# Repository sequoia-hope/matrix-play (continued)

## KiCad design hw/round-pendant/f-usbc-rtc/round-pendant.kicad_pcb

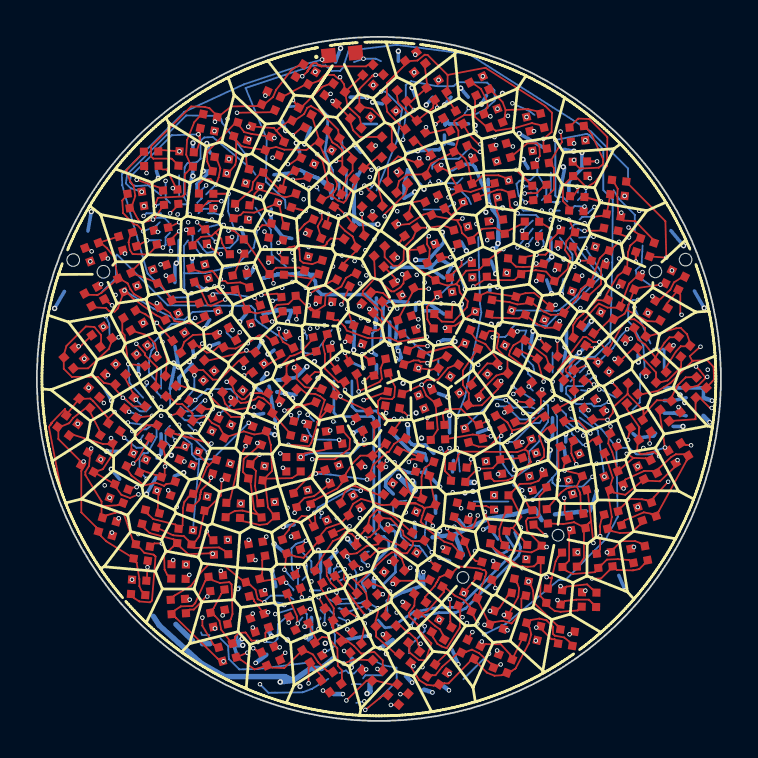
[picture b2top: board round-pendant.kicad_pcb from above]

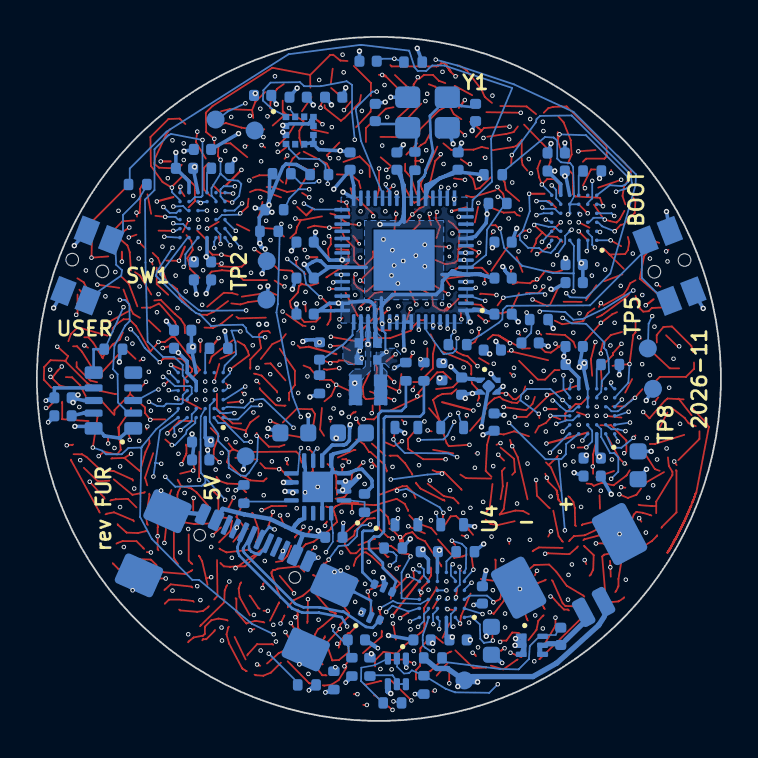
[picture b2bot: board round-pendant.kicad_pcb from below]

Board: 8 copper layers, 38.0 x 38.0 mm, 346 parts (110 on the bottom side), 187 nets.

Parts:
BT1: A1251WR-S-2P; Molex_PicoBlade_53261-0271_1x02-1MP_P1.25mm_Horizontal
C1, C3, C4, C31, C34, C41, C44, C51, C54, C61, C64, C71, C74, C76: 1u; C_0402_1005Metric
C2, C30, C40: 22u; C_0603_1608Metric
C5: 10u; C_0603_1608Metric
C6, C7, C8, C9, C10, C11, C12, C13, C14, C20, C21, C22, C25, C27, C32, C33, C35, C42, C43, C52, C53, C62, C63, C70, C72, C73, C75: 100n; C_0402_1005Metric
C16, C18: 4.7u; C_0402_1005Metric_small_pads
C17, C19, C26: 4.7u; C_0402_1005Metric
C23, C24: 15p; C_0402_1005Metric
D1, D2, D3, D4, D5, D6, D7, D8, D9, D10, D11, D12, D13, D14, D15, D16, D17, D18, D19, D20, D21, D22, D23, D24, D25, D26, D27, D28, D29, D30, D31, D32, D33, D34, D35, D36, D37, D38, D39, D40, D41, D42, D43, D44, D45, D46, D47, D48, D49, D50, D51, D52, D53, D54, D55, D56, D57, D58, D59, D60, D61, D62, D63, D64, D65, D66, D67, D68, D69, D70, D71, D72, D73, D74, D75, D76, D77, D78, D79, D80, D81, D82, D83, D84, D85, D86, D87, D88, D89, D90, D91, D92, D93, D94, D95, D96, D97, D98, D99, D100, D101, D102, D103, D104, D105, D106, D107, D108, D109, D110, D111, D112, D113, D114, D115, D116, D117, D118, D119, D120, D121, D122, D123, D124, D125, D126, D127, D128, D129, D130, D131, D132, D133, D134, D135, D136, D137, D138, D139, D140, D141, D142, D143, D144, D145, D146, D147, D148, D149, D150, D151, D152, D153, D154, D155, D156, D157, D158, D159, D160, D161, D162, D163, D164, D165, D166, D167, D168, D169, D170, D171, D172, D173, D174, D175, D176, D177, D178, D179, D180, D181, D182, D183, D184, D185, D186, D187, D188, D189, D190, D191, D192, D193, D194, D195, D196, D197, D198, D199, D200, D201, D202, D203, D204, D205, D206, D207, D208, D209, D210, D211, D212, D213, D214, D215, D216, D217, D218, D219, D220, D221, D222, D223, D224, D225, D226, D227, D228, D229, D230, D231, D232, D233, D234, D235: RGB; LED_XL-1010RGB
J1: TYPE-C-31-M-22; USB_C_Receptacle_Hroparts_TYPE-C-31-M-22
L1: 3.3u; L_pol_2016
Q1: NTZD3155C; SOT-563
Q2: ALS-PT19; SENSOR_ALS-PT19
R1, R2: 5.1k; R_0402_1005Metric
R3: 10k; R_0402_1005Metric
R4: 3k; R_0402_1005Metric
R5: 3.6k; R_0402_1005Metric
R6, R7, R9, R10, R11, R12, R31, R32: 100k; R_0402_1005Metric
R8: 100R; R_0402_1005Metric
R13: 33R; R_0402_1005Metric
R14, R15: 27R; R_0402_1005Metric
R16, R17, R18, R21, R22: 1k; R_0402_1005Metric
R19, R20: 4.7k; R_0402_1005Metric
R30, R33, R50, R60, R70: 30k; R_0402_1005Metric
R43: 22k; R_0402_1005Metric
SW1: USER / WAKE; SW_Panasonic_EVQP7C
SW2: BOOTSEL; SW_Panasonic_EVQP7C
TP1: VSYS; TestPoint_Pad_D1.0mm
TP2: +3V3; TestPoint_Pad_D1.0mm
TP3: VBAT; TestPoint_Pad_D1.0mm
TP4: 1V1; TestPoint_Pad_D1.0mm
TP5: RUN; TestPoint_Pad_D1.0mm
TP6: SWCLK; TestPoint_Pad_D1.0mm
TP7: SWDIO; TestPoint_Pad_D1.0mm
TP8: GND; TestPoint_Pad_D1.0mm
U1, U2, U10, U11, U12: IS31FL3745; WLCSP-36_2.9x2.9mm_P0.5mm
U3: RP2350A; RP2350-QFN-60-1EP_7x7_P0.4mm_EP3.4x3.4mm_ThermalVias
U4: W25Q128JVPIQ; WSON-8_6x5mm_P1.27mm_NoEPCopper
U5: BQ24073; QFN-16-1EP_3x3mm_P0.5mm_EP1.7x1.7mm
U6: TPS7A0233; Texas_X2SON-4_1x1mm_P0.65mm
U7: USBLC6-2P6; SOT-666
U8: XB9901A; XySemi_DFN-6_1.8x1.4mm
U9: LIS2DW12; LGA-12_2x2mm_P0.5mm
U13: RX8130CE; Seiko_Epson_RX8130CE_3.2x2.5mm_P0.7mm
Y1: 12MHz; Crystal_SMD_3225-4Pin_3.2x2.5mm

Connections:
+1V1: C18.1, C19.1, C20.1, C21.1, L1.1, TP4.1, U3.6, U3.23, U3.39, U3.50
+3V3: C4.1, C8.1, C9.1, C10.1, C11.1, C12.1, C13.1, C14.1, C16.1, C22.1, C25.1, C26.1, C27.1, C75.1, R6.1, R7.1, R13.1, R19.1, R20.1, R21.1, R22.1, R32.1, TP2.1, U3.1, U3.11, U3.20, U3.30, U3.38, U3.44, U3.45, U3.49, U3.53, U3.54, U4.8, U5.6, U6.1, U9.2, U9.3, U9.9, U9.10, U13.1, U13.8, U13.10
/Driver 1 and matrix/CS1_1: D1.4, D2.4, D3.4, D4.4, D5.4, D6.4, D7.4, D8.4, U1.B2
/Driver 1 and matrix/CS1_2: D1.2, D2.2, D3.2, D4.2, D5.2, D6.2, D7.2, D8.2, U1.B3
/Driver 1 and matrix/CS1_3: D1.1, D2.1, D3.1, D4.1, D5.1, D6.1, D7.1, D8.1, U1.C3
/Driver 1 and matrix/CS1_4: D9.4, D10.4, D11.4, D12.4, D13.4, D14.4, D15.4, D16.4, U1.C2
/Driver 1 and matrix/CS1_5: D9.2, D10.2, D11.2, D12.2, D13.2, D14.2, D15.2, D16.2, U1.D2
/Driver 1 and matrix/CS1_6: D9.1, D10.1, D11.1, D12.1, D13.1, D14.1, D15.1, D16.1, U1.D1
/Driver 1 and matrix/CS1_7: D17.4, D18.4, D19.4, D20.4, D21.4, D22.4, D23.4, D24.4, U1.E2
/Driver 1 and matrix/CS1_8: D17.2, D18.2, D19.2, D20.2, D21.2, D22.2, D23.2, D24.2, U1.E1
/Driver 1 and matrix/CS1_9: D17.1, D18.1, D19.1, D20.1, D21.1, D22.1, D23.1, D24.1, U1.F1
/Driver 1 and matrix/CS1_10: D25.4, D26.4, D27.4, D28.4, D29.4, D30.4, D31.4, D32.4, U1.F6
/Driver 1 and matrix/CS1_11: D25.2, D26.2, D27.2, D28.2, D29.2, D30.2, D31.2, D32.2, U1.E6
/Driver 1 and matrix/CS1_12: D25.1, D26.1, D27.1, D28.1, D29.1, D30.1, D31.1, D32.1, U1.D5
/Driver 1 and matrix/CS1_13: D33.4, D34.4, D35.4, D36.4, D37.4, D38.4, D39.4, D40.4, U1.D6
/Driver 1 and matrix/CS1_14: D33.2, D34.2, D35.2, D36.2, D37.2, D38.2, D39.2, D40.2, U1.C4
/Driver 1 and matrix/CS1_15: D33.1, D34.1, D35.1, D36.1, D37.1, D38.1, D39.1, D40.1, U1.C6
/Driver 1 and matrix/CS1_16: D41.4, D42.4, D43.4, D44.4, D45.4, D46.4, D47.4, U1.C5
/Driver 1 and matrix/CS1_17: D41.2, D42.2, D43.2, D44.2, D45.2, D46.2, D47.2, U1.B4
/Driver 1 and matrix/CS1_18: D41.1, D42.1, D43.1, D44.1, D45.1, D46.1, D47.1, U1.B5
/Driver 1 and matrix/SW1_1: D1.3, D9.3, D17.3, D25.3, D33.3, D41.3, U1.A2
/Driver 1 and matrix/SW1_2: D2.3, D10.3, D18.3, D26.3, D34.3, D42.3, U1.A4
/Driver 1 and matrix/SW1_3: D3.3, D11.3, D19.3, D27.3, D35.3, D43.3, U1.A1
/Driver 1 and matrix/SW1_4: D4.3, D12.3, D20.3, D28.3, D36.3, D44.3, U1.A5
/Driver 1 and matrix/SW1_5: D5.3, D13.3, D21.3, D29.3, D37.3, D45.3, U1.B1
/Driver 1 and matrix/SW1_6: D6.3, D14.3, D22.3, D30.3, D38.3, D46.3, U1.A6
/Driver 1 and matrix/SW1_7: D7.3, D15.3, D23.3, D31.3, D39.3, D47.3, U1.C1
/Driver 1 and matrix/SW1_8: D8.3, D16.3, D24.3, D32.3, D40.3, U1.B6
/Driver 2 and matrix/CS2_1: D48.4, D49.4, D50.4, D51.4, D52.4, D53.4, D54.4, D55.4, U2.B2
/Driver 2 and matrix/CS2_2: D48.2, D49.2, D50.2, D51.2, D52.2, D53.2, D54.2, D55.2, U2.B3
/Driver 2 and matrix/CS2_3: D48.1, D49.1, D50.1, D51.1, D52.1, D53.1, D54.1, D55.1, U2.C3
/Driver 2 and matrix/CS2_4: D56.4, D57.4, D58.4, D59.4, D60.4, D61.4, D62.4, D63.4, U2.C2
/Driver 2 and matrix/CS2_5: D56.2, D57.2, D58.2, D59.2, D60.2, D61.2, D62.2, D63.2, U2.D2
/Driver 2 and matrix/CS2_6: D56.1, D57.1, D58.1, D59.1, D60.1, D61.1, D62.1, D63.1, U2.D1
/Driver 2 and matrix/CS2_7: D64.4, D65.4, D66.4, D67.4, D68.4, D69.4, D70.4, D71.4, U2.E2
/Driver 2 and matrix/CS2_8: D64.2, D65.2, D66.2, D67.2, D68.2, D69.2, D70.2, D71.2, U2.E1
/Driver 2 and matrix/CS2_9: D64.1, D65.1, D66.1, D67.1, D68.1, D69.1, D70.1, D71.1, U2.F1
/Driver 2 and matrix/CS2_10: D72.4, D73.4, D74.4, D75.4, D76.4, D77.4, D78.4, D79.4, U2.F6
/Driver 2 and matrix/CS2_11: D72.2, D73.2, D74.2, D75.2, D76.2, D77.2, D78.2, D79.2, U2.E6
/Driver 2 and matrix/CS2_12: D72.1, D73.1, D74.1, D75.1, D76.1, D77.1, D78.1, D79.1, U2.D5
/Driver 2 and matrix/CS2_13: D80.4, D81.4, D82.4, D83.4, D84.4, D85.4, D86.4, D87.4, U2.D6
/Driver 2 and matrix/CS2_14: D80.2, D81.2, D82.2, D83.2, D84.2, D85.2, D86.2, D87.2, U2.C4
/Driver 2 and matrix/CS2_15: D80.1, D81.1, D82.1, D83.1, D84.1, D85.1, D86.1, D87.1, U2.C6
/Driver 2 and matrix/CS2_16: D88.4, D89.4, D90.4, D91.4, D92.4, D93.4, D94.4, U2.C5
/Driver 2 and matrix/CS2_17: D88.2, D89.2, D90.2, D91.2, D92.2, D93.2, D94.2, U2.B4
/Driver 2 and matrix/CS2_18: D88.1, D89.1, D90.1, D91.1, D92.1, D93.1, D94.1, U2.B5
/Driver 2 and matrix/SW2_1: D48.3, D56.3, D64.3, D72.3, D80.3, D88.3, U2.A2
/Driver 2 and matrix/SW2_2: D49.3, D57.3, D65.3, D73.3, D81.3, D89.3, U2.A4
/Driver 2 and matrix/SW2_3: D50.3, D58.3, D66.3, D74.3, D82.3, D90.3, U2.A1
/Driver 2 and matrix/SW2_4: D51.3, D59.3, D67.3, D75.3, D83.3, D91.3, U2.A5
/Driver 2 and matrix/SW2_5: D52.3, D60.3, D68.3, D76.3, D84.3, D92.3, U2.B1
/Driver 2 and matrix/SW2_6: D53.3, D61.3, D69.3, D77.3, D85.3, D93.3, U2.A6
/Driver 2 and matrix/SW2_7: D54.3, D62.3, D70.3, D78.3, D86.3, D94.3, U2.C1
/Driver 2 and matrix/SW2_8: D55.3, D63.3, D71.3, D79.3, D87.3, U2.B6
/Driver 3 and matrix/CS3_1: D95.4, D96.4, D97.4, D98.4, D99.4, D100.4, D101.4, D102.4, U10.B2
/Driver 3 and matrix/CS3_2: D95.2, D96.2, D97.2, D98.2, D99.2, D100.2, D101.2, D102.2, U10.B3
/Driver 3 and matrix/CS3_3: D95.1, D96.1, D97.1, D98.1, D99.1, D100.1, D101.1, D102.1, U10.C3
/Driver 3 and matrix/CS3_4: D103.4, D104.4, D105.4, D106.4, D107.4, D108.4, D109.4, D110.4, U10.C2
/Driver 3 and matrix/CS3_5: D103.2, D104.2, D105.2, D106.2, D107.2, D108.2, D109.2, D110.2, U10.D2
/Driver 3 and matrix/CS3_6: D103.1, D104.1, D105.1, D106.1, D107.1, D108.1, D109.1, D110.1, U10.D1
/Driver 3 and matrix/CS3_7: D111.4, D112.4, D113.4, D114.4, D115.4, D116.4, D117.4, D118.4, U10.E2
/Driver 3 and matrix/CS3_8: D111.2, D112.2, D113.2, D114.2, D115.2, D116.2, D117.2, D118.2, U10.E1
/Driver 3 and matrix/CS3_9: D111.1, D112.1, D113.1, D114.1, D115.1, D116.1, D117.1, D118.1, U10.F1
/Driver 3 and matrix/CS3_10: D119.4, D120.4, D121.4, D122.4, D123.4, D124.4, D125.4, D126.4, U10.F6
/Driver 3 and matrix/CS3_11: D119.2, D120.2, D121.2, D122.2, D123.2, D124.2, D125.2, D126.2, U10.E6
/Driver 3 and matrix/CS3_12: D119.1, D120.1, D121.1, D122.1, D123.1, D124.1, D125.1, D126.1, U10.D5
/Driver 3 and matrix/CS3_13: D127.4, D128.4, D129.4, D130.4, D131.4, D132.4, D133.4, D134.4, U10.D6
/Driver 3 and matrix/CS3_14: D127.2, D128.2, D129.2, D130.2, D131.2, D132.2, D133.2, D134.2, U10.C4
/Driver 3 and matrix/CS3_15: D127.1, D128.1, D129.1, D130.1, D131.1, D132.1, D133.1, D134.1, U10.C6
/Driver 3 and matrix/CS3_16: D135.4, D136.4, D137.4, D138.4, D139.4, D140.4, D141.4, U10.C5
/Driver 3 and matrix/CS3_17: D135.2, D136.2, D137.2, D138.2, D139.2, D140.2, D141.2, U10.B4
/Driver 3 and matrix/CS3_18: D135.1, D136.1, D137.1, D138.1, D139.1, D140.1, D141.1, U10.B5
/Driver 3 and matrix/SW3_1: D95.3, D103.3, D111.3, D119.3, D127.3, D135.3, U10.A2
/Driver 3 and matrix/SW3_2: D96.3, D104.3, D112.3, D120.3, D128.3, D136.3, U10.A4
/Driver 3 and matrix/SW3_3: D97.3, D105.3, D113.3, D121.3, D129.3, D137.3, U10.A1
/Driver 3 and matrix/SW3_4: D98.3, D106.3, D114.3, D122.3, D130.3, D138.3, U10.A5
/Driver 3 and matrix/SW3_5: D99.3, D107.3, D115.3, D123.3, D131.3, D139.3, U10.B1
/Driver 3 and matrix/SW3_6: D100.3, D108.3, D116.3, D124.3, D132.3, D140.3, U10.A6
/Driver 3 and matrix/SW3_7: D101.3, D109.3, D117.3, D125.3, D133.3, D141.3, U10.C1
/Driver 3 and matrix/SW3_8: D102.3, D110.3, D118.3, D126.3, D134.3, U10.B6
/Driver 4 and matrix/CS4_1: D142.4, D143.4, D144.4, D145.4, D146.4, D147.4, D148.4, D149.4, U11.B2
/Driver 4 and matrix/CS4_2: D142.2, D143.2, D144.2, D145.2, D146.2, D147.2, D148.2, D149.2, U11.B3
/Driver 4 and matrix/CS4_3: D142.1, D143.1, D144.1, D145.1, D146.1, D147.1, D148.1, D149.1, U11.C3
/Driver 4 and matrix/CS4_4: D150.4, D151.4, D152.4, D153.4, D154.4, D155.4, D156.4, D157.4, U11.C2
/Driver 4 and matrix/CS4_5: D150.2, D151.2, D152.2, D153.2, D154.2, D155.2, D156.2, D157.2, U11.D2
/Driver 4 and matrix/CS4_6: D150.1, D151.1, D152.1, D153.1, D154.1, D155.1, D156.1, D157.1, U11.D1
/Driver 4 and matrix/CS4_7: D158.4, D159.4, D160.4, D161.4, D162.4, D163.4, D164.4, D165.4, U11.E2
/Driver 4 and matrix/CS4_8: D158.2, D159.2, D160.2, D161.2, D162.2, D163.2, D164.2, D165.2, U11.E1
/Driver 4 and matrix/CS4_9: D158.1, D159.1, D160.1, D161.1, D162.1, D163.1, D164.1, D165.1, U11.F1
/Driver 4 and matrix/CS4_10: D166.4, D167.4, D168.4, D169.4, D170.4, D171.4, D172.4, D173.4, U11.F6
/Driver 4 and matrix/CS4_11: D166.2, D167.2, D168.2, D169.2, D170.2, D171.2, D172.2, D173.2, U11.E6
/Driver 4 and matrix/CS4_12: D166.1, D167.1, D168.1, D169.1, D170.1, D171.1, D172.1, D173.1, U11.D5
/Driver 4 and matrix/CS4_13: D174.4, D175.4, D176.4, D177.4, D178.4, D179.4, D180.4, D181.4, U11.D6
/Driver 4 and matrix/CS4_14: D174.2, D175.2, D176.2, D177.2, D178.2, D179.2, D180.2, D181.2, U11.C4
/Driver 4 and matrix/CS4_15: D174.1, D175.1, D176.1, D177.1, D178.1, D179.1, D180.1, D181.1, U11.C6
/Driver 4 and matrix/CS4_16: D182.4, D183.4, D184.4, D185.4, D186.4, D187.4, D188.4, U11.C5
/Driver 4 and matrix/CS4_17: D182.2, D183.2, D184.2, D185.2, D186.2, D187.2, D188.2, U11.B4
/Driver 4 and matrix/CS4_18: D182.1, D183.1, D184.1, D185.1, D186.1, D187.1, D188.1, U11.B5
/Driver 4 and matrix/SW4_1: D142.3, D150.3, D158.3, D166.3, D174.3, D182.3, U11.A2
/Driver 4 and matrix/SW4_2: D143.3, D151.3, D159.3, D167.3, D175.3, D183.3, U11.A4
/Driver 4 and matrix/SW4_3: D144.3, D152.3, D160.3, D168.3, D176.3, D184.3, U11.A1
/Driver 4 and matrix/SW4_4: D145.3, D153.3, D161.3, D169.3, D177.3, D185.3, U11.A5
/Driver 4 and matrix/SW4_5: D146.3, D154.3, D162.3, D170.3, D178.3, D186.3, U11.B1
/Driver 4 and matrix/SW4_6: D147.3, D155.3, D163.3, D171.3, D179.3, D187.3, U11.A6
/Driver 4 and matrix/SW4_7: D148.3, D156.3, D164.3, D172.3, D180.3, D188.3, U11.C1
/Driver 4 and matrix/SW4_8: D149.3, D157.3, D165.3, D173.3, D181.3, U11.B6
/Driver 5 and matrix/CS5_1: D189.4, D190.4, D191.4, D192.4, D193.4, D194.4, D195.4, D196.4, U12.B2
/Driver 5 and matrix/CS5_2: D189.2, D190.2, D191.2, D192.2, D193.2, D194.2, D195.2, D196.2, U12.B3
/Driver 5 and matrix/CS5_3: D189.1, D190.1, D191.1, D192.1, D193.1, D194.1, D195.1, D196.1, U12.C3
/Driver 5 and matrix/CS5_4: D197.4, D198.4, D199.4, D200.4, D201.4, D202.4, D203.4, D204.4, U12.C2
/Driver 5 and matrix/CS5_5: D197.2, D198.2, D199.2, D200.2, D201.2, D202.2, D203.2, D204.2, U12.D2
/Driver 5 and matrix/CS5_6: D197.1, D198.1, D199.1, D200.1, D201.1, D202.1, D203.1, D204.1, U12.D1
/Driver 5 and matrix/CS5_7: D205.4, D206.4, D207.4, D208.4, D209.4, D210.4, D211.4, D212.4, U12.E2
/Driver 5 and matrix/CS5_8: D205.2, D206.2, D207.2, D208.2, D209.2, D210.2, D211.2, D212.2, U12.E1
/Driver 5 and matrix/CS5_9: D205.1, D206.1, D207.1, D208.1, D209.1, D210.1, D211.1, D212.1, U12.F1
/Driver 5 and matrix/CS5_10: D213.4, D214.4, D215.4, D216.4, D217.4, D218.4, D219.4, D220.4, U12.F6
/Driver 5 and matrix/CS5_11: D213.2, D214.2, D215.2, D216.2, D217.2, D218.2, D219.2, D220.2, U12.E6
/Driver 5 and matrix/CS5_12: D213.1, D214.1, D215.1, D216.1, D217.1, D218.1, D219.1, D220.1, U12.D5
/Driver 5 and matrix/CS5_13: D221.4, D222.4, D223.4, D224.4, D225.4, D226.4, D227.4, D228.4, U12.D6
/Driver 5 and matrix/CS5_14: D221.2, D222.2, D223.2, D224.2, D225.2, D226.2, D227.2, D228.2, U12.C4
/Driver 5 and matrix/CS5_15: D221.1, D222.1, D223.1, D224.1, D225.1, D226.1, D227.1, D228.1, U12.C6
/Driver 5 and matrix/CS5_16: D229.4, D230.4, D231.4, D232.4, D233.4, D234.4, D235.4, U12.C5
/Driver 5 and matrix/CS5_17: D229.2, D230.2, D231.2, D232.2, D233.2, D234.2, D235.2, U12.B4
/Driver 5 and matrix/CS5_18: D229.1, D230.1, D231.1, D232.1, D233.1, D234.1, D235.1, U12.B5
/Driver 5 and matrix/SW5_1: D189.3, D197.3, D205.3, D213.3, D221.3, D229.3, U12.A2
/Driver 5 and matrix/SW5_2: D190.3, D198.3, D206.3, D214.3, D222.3, D230.3, U12.A4
/Driver 5 and matrix/SW5_3: D191.3, D199.3, D207.3, D215.3, D223.3, D231.3, U12.A1
/Driver 5 and matrix/SW5_4: D192.3, D200.3, D208.3, D216.3, D224.3, D232.3, U12.A5
/Driver 5 and matrix/SW5_5: D193.3, D201.3, D209.3, D217.3, D225.3, D233.3, U12.B1
/Driver 5 and matrix/SW5_6: D194.3, D202.3, D210.3, D218.3, D226.3, D234.3, U12.A6
/Driver 5 and matrix/SW5_7: D195.3, D203.3, D211.3, D219.3, D227.3, D235.3, U12.C1
/Driver 5 and matrix/SW5_8: D196.3, D204.3, D212.3, D220.3, D228.3, U12.B6
/MCU/ACC_INT: U3.14, U9.12
/MCU/ACC_SCL: R19.2, U3.5, U9.1, U13.2
/MCU/ACC_SDA: R20.2, U3.4, U9.4, U13.3
/MCU/BTN: R18.1, U3.15
/MCU/LIGHT: C70.1, Q2.2, R43.1, U3.41
/MCU/LIGHT_PWR: Q2.1, U3.3
/MCU/QSPI_SCLK: U3.56, U4.6
/MCU/QSPI_SD0: U3.57, U4.5
/MCU/QSPI_SD1: U3.59, U4.2
/MCU/QSPI_SD2: U3.58, U4.3
/MCU/QSPI_SD3: U3.55, U4.7
/MCU/QSPI_SS: R16.1, U3.60, U4.1
/MCU/RTC_INT: R32.2, U3.31, U13.6
/MCU/RTC_VOUT: C76.1, U13.9
/MCU/RUN: TP5.1, U3.26
/MCU/SWCLK: TP6.1, U3.24
/MCU/SWDIO: TP7.1, U3.25
/MCU/USB_DM_MCU: R14.2, U3.51
/MCU/USB_DP_MCU: R15.2, U3.52
/MCU/VREG_AVDD: C17.1, R13.2, U3.46
/MCU/VREG_LX: L1.2, U3.48
/Power/BAT_N: BT1.2, C6.2, U8.4, U8.5
/Power/CC1: J1.A5, R1.1
/Power/CC2: J1.B5, R2.1
/Power/USB_DM_C: J1.A7, J1.B7, U7.1
/Power/USB_DP_C: J1.A6, J1.B6, U7.3
CHG: R7.2, U3.16, U5.9
GND: BT1.MP, C1.2, C2.2, C3.2, C4.2, C5.2, C7.2, C8.2, C9.2, C10.2, C11.2, C12.2, C13.2, C14.2, C16.2, C17.2, C18.2, C19.2, C20.2, C21.2, C22.2, C23.2, C24.2, C25.2, C26.2, C27.2, C30.2, C31.2, C32.2, C33.2, C34.2, C35.2, C40.2, C41.2, C42.2, C43.2, C44.2, C51.2, C52.2, C53.2, C54.2, C61.2, C62.2, C63.2, C64.2, C70.2, C71.2, C72.2, C73.2, C74.2, C75.2, C76.2, J1.A1B12, J1.B1A12, J1.S1, Q1.1, R1.2, R2.2, R3.2, R4.2, R5.2, R9.2, R12.2, R30.2, R31.2, R33.2, R43.2, R50.2, R60.2, R70.2, SW1.2, SW2.2, TP8.1, U1.D4, U1.E4, U1.F4, U2.E4, U2.F4, U3.47, U3.61, U4.4, U5.4, U5.5, U5.8, U5.15, U5.17, U6.2, U6.5, U7.2, U8.1, U8.2, U8.3, U9.6, U9.7, U9.8, U10.F4, U11.F4, U12.F4, U13.7, Y1.2, Y1.4
I2C_SCL: R22.2, U1.E3, U2.E3, U3.8, U10.D4, U10.E3, U10.E4, U11.E3, U11.E4, U12.E3
I2C_SDA: R21.2, U1.D3, U2.D3, U2.D4, U3.7, U10.D3, U11.D3, U11.D4, U12.D3
LED_SDB: C35.1, R31.1, U1.E5, U2.E5, U3.9, U10.E5, U11.E5, U12.E5
unnamed: C24.1, R17.1, Y1.3
unnamed: Q1.5, Q1.6, R10.2
unnamed: Q1.3, R11.1
unnamed: R16.2, SW2.1
unnamed: R18.2, SW1.1
unnamed: R30.1, U1.F3
unnamed: R33.1, U2.F3
unnamed: C23.1, U3.21, Y1.1
unnamed: R17.2, U3.22
unnamed: R5.1, U5.12
unnamed: R4.1, U5.16
unnamed: R3.1, U5.1
unnamed: C6.1, R8.2, U8.6
unnamed: R50.1, U10.F3
unnamed: R60.1, U11.F3
unnamed: R70.1, U12.F3
PGOOD: R6.2, U3.17, U5.7
USB_DM: R14.1, U7.6
USB_DP: R15.1, U7.4
VBAT: BT1.1, C5.1, Q1.4, R8.1, R10.1, TP3.1, U5.2, U5.3
VBAT_EN: Q1.2, R9.1, U3.18
VBAT_SENSE: C7.1, R11.2, R12.1, U3.40
VBUS: C1.1, J1.A4B9, J1.B4A9, U5.13, U7.5
VSYS: C2.1, C3.1, C30.1, C31.1, C32.1, C33.1, C34.1, C40.1, C41.1, C42.1, C43.1, C44.1, C51.1, C52.1, C53.1, C54.1, C61.1, C62.1, C63.1, C64.1, C71.1, C72.1, C73.1, C74.1, TP1.1, U1.A3, U1.F5, U2.A3, U2.F5, U5.10, U5.11, U6.3, U6.4, U10.A3, U10.F5, U11.A3, U11.F5, U12.A3, U12.D4, U12.E4, U12.F5

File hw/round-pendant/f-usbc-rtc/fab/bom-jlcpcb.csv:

Comment,Designator,Footprint,LCSC Part #,MPN,Manufacturer
A1251WR-S-2P,BT1,Molex_PicoBlade_53261-0271_1x02-1MP_P1.25mm_Horizontal,C225111,A1251WR-S-2P,CJT
1u,"C1,C3,C4,C31,C34,C41,C44,C51,C54,C61,C64,C71,C74,C76",C_0402_1005Metric,C52923,CL05A105KA5NQNC,Samsung Electro-Mechanics
22u,"C2,C30,C40",C_0603_1608Metric,C86295,CL10A226MP8NUNE,Samsung Electro-Mechanics
10u,C5,C_0603_1608Metric,C19702,CL10A106KP8NNNC,Samsung Electro-Mechanics
100n,"C6,C7,C8,C9,C10,C11,C12,C13,C14,C20,C21,C22,C25,C27,C32,C33,C35,C42,C43,C52,C53,C62,C63,C70,C72,C73,C75",C_0402_1005Metric,C1525,CL05B104KO5NNNC,Samsung Electro-Mechanics
4.7u,"C16,C18",C_0402_1005Metric_small_pads,C23733,CL05A475MP5NRNC,Samsung Electro-Mechanics
4.7u,"C17,C19,C26",C_0402_1005Metric,C23733,CL05A475MP5NRNC,Samsung Electro-Mechanics
15p,"C23,C24",C_0402_1005Metric,C1548,0402CG150J500NT,FH
RGB,"D1,D2,D3,D4,D5,D6,D7,D8,D9,D10,D11,D12,D13,D14,D15,D16,D17,D18,D19,D20,D21,D22,D23,D24,D25,D26,D27,D28,D29,D30,D31,D32,D33,D34,D35,D36,D37,D38,D39,D40,D41,D42,D43,D44,D45,D46,D47,D48,D49,D50,D51,D52,D53,D54,D55,D56,D57,D58,D59,D60,D61,D62,D63,D64,D65,D66,D67,D68,D69,D70,D71,D72,D73,D74,D75,D76,D77,D78,D79,D80,D81,D82,D83,D84,D85,D86,D87,D88,D89,D90,D91,D92,D93,D94,D95,D96,D97,D98,D99,D100,D101,D102,D103,D104,D105,D106,D107,D108,D109,D110,D111,D112,D113,D114,D115,D116,D117,D118,D119,D120,D121,D122,D123,D124,D125,D126,D127,D128,D129,D130,D131,D132,D133,D134,D135,D136,D137,D138,D139,D140,D141,D142,D143,D144,D145,D146,D147,D148,D149,D150,D151,D152,D153,D154,D155,D156,D157,D158,D159,D160,D161,D162,D163,D164,D165,D166,D167,D168,D169,D170,D171,D172,D173,D174,D175,D176,D177,D178,D179,D180,D181,D182,D183,D184,D185,D186,D187,D188,D189,D190,D191,D192,D193,D194,D195,D196,D197,D198,D199,D200,D201,D202,D203,D204,D205,D206,D207,D208,D209,D210,D211,D212,D213,D214,D215,D216,D217,D218,D219,D220,D221,D222,D223,D224,D225,D226,D227,D228,D229,D230,D231,D232,D233,D234,D235",LED_XL-1010RGB,C965834,XL-1010RGB-YG,XINGLIGHT
TYPE-C-31-M-22,J1,USB_C_Receptacle_Hroparts_TYPE-C-31-M-22,C530612,TYPE-C-31-M-22,Korean Hroparts Elec
3.3u,L1,L_pol_2016,C42411119,AOTA-B201610S3R3-101-T,Abracon
NTZD3155C,Q1,SOT-563,C236117,NTZD3155CT1G,onsemi
ALS-PT19,Q2,SENSOR_ALS-PT19,C146233,ALS-PT19-315C/L177/TR8,EVERLIGHT
5.1k,"R1,R2",R_0402_1005Metric,C25905,0402WGF5101TCE,UNI-ROYAL
10k,R3,R_0402_1005Metric,C25744,0402WGF1002TCE,UNI-ROYAL
3k,R4,R_0402_1005Metric,C25784,0402WGF3001TCE,UNI-ROYAL
3.6k,R5,R_0402_1005Metric,C25891,0402WGF3601TCE,UNI-ROYAL
100k,"R6,R7,R9,R10,R11,R12,R31,R32",R_0402_1005Metric,C25741,0402WGF1003TCE,UNI-ROYAL
100R,R8,R_0402_1005Metric,C25076,0402WGF1000TCE,UNI-ROYAL
33R,R13,R_0402_1005Metric,C25105,0402WGF330JTCE,UNI-ROYAL
27R,"R14,R15",R_0402_1005Metric,C25100,0402WGF270JTCE,UNI-ROYAL
1k,"R16,R17,R18,R21,R22",R_0402_1005Metric,C11702,0402WGF1001TCE,UNI-ROYAL
4.7k,"R19,R20",R_0402_1005Metric,C25900,0402WGF4701TCE,UNI-ROYAL
30k,"R30,R33,R50,R60,R70",R_0402_1005Metric,C25776,0402WGF3002TCE,UNI-ROYAL
22k,R43,R_0402_1005Metric,C25768,0402WGF2202TCE,UNI-ROYAL
USER / WAKE,SW1,SW_Panasonic_EVQP7C,C388883,EVQP7C01P,PANASONIC
BOOTSEL,SW2,SW_Panasonic_EVQP7C,C388883,EVQP7C01P,PANASONIC
IS31FL3745,"U1,U2,U10,U11,U12",WLCSP-36_2.9x2.9mm_P0.5mm,C2678907,IS31FL3745-CLS4-TR,ISSI
RP2350A,U3,RP2350-QFN-60-1EP_7x7_P0.4mm_EP3.4x3.4mm_ThermalVias,C42411118,RP2350A,Raspberry Pi
W25Q128JVPIQ,U4,WSON-8_6x5mm_P1.27mm_NoEPCopper,C190862,W25Q128JVPIQ,Winbond
BQ24073,U5,QFN-16-1EP_3x3mm_P0.5mm_EP1.7x1.7mm,C15220,BQ24073RGTR,Texas Instruments
TPS7A0233,U6,Texas_X2SON-4_1x1mm_P0.65mm,C2860046,TPS7A0233PDQNR,Texas Instruments
USBLC6-2P6,U7,SOT-666,C15999,USBLC6-2P6,STMicroelectronics
XB9901A,U8,XySemi_DFN-6_1.8x1.4mm,C669687,XB9901A,XySemi
LIS2DW12,U9,LGA-12_2x2mm_P0.5mm,C189624,LIS2DW12TR,STMicroelectronics
RX8130CE,U13,Seiko_Epson_RX8130CE_3.2x2.5mm_P0.7mm,C1542426,RX8130CE:BB,Seiko Epson
12MHz,Y1,Crystal_SMD_3225-4Pin_3.2x2.5mm,C20625731,ABM8-272-T3,Abracon

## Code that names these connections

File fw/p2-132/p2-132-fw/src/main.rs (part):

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//! - Enables Cortex-M33 VFPv5 FPU, 12 MHz XOSC, and 150 MHz PLL_SYS + 1 us TIMER0 tick.
//! - Configures PADS_QSPI SLEWFAST=0 (Phase P1 EM finding: cuts In2.Cu QSPI crosstalk 5.1x).
//! - Drives U1 (0x20, North 6x11 D1..D66) and U2 (0x25, South 6x11 D67..D132) over 1.04 MHz Fm+
//!   open-drain I2C on GPIO4/GPIO5 using RP2350 PIO0 SM0 + DMA Channel 0 (DREQ_PIO0_TX0 = 0).
//! - Programs AW20198QNR EM-derived registers:
//!     * SRCR (0x2B) = 0x07 (6 ns rise / 10 ns fall -> 3.4x lower I2C glitch & -30.4 dB @ 300 MHz EMI)
//!     * PCCR (0x29) = 0x02 (Three-Phase PWM stagger -> 5.4x lower VSYS AC ripple at North U1)
//!     * SSCR (0x28) = 0x15 (Spread-spectrum clock modulation enabled)
//!     * DGCR (0x02) = 0x44 (Off-time 4 kOhm CS pull-up / 2 kOhm SW bleed de-ghosting)
//!     * SL0..197    = D65 white-balanced per-die current scaling (R=255, G=96, B=220)
//! - Polls LIS2DW12TR (0x19) on GPIO2/GPIO3 (400 kHz open-drain SIO I2C), SW1 button (GPIO11),
//!   BQ24073 status (GPIO12 CHG, GPIO13 PGOOD), and 8x-oversampled ADC0/ADC1 (VBAT_SENSE / LIGHT,
//!   averaging out the 148 mV VREG_LX buck crossover spikes discovered in Phase P2!).
//! - Applies our Phase P4 PDN-derived GCC(VBAT) foldback curve below 3.65 V to prevent North Blue/Green dropout.
//! - Dual-core pipelined architecture:
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const RESET_TIMER0: u32     = 1 << 23;

// p2-132 GPIO Pinout
const PIN_LIGHT_PWR: u32 = 1;
const PIN_ACC_SDA: u32   = 2;
const PIN_ACC_SCL: u32   = 3;
const PIN_I2C_SDA: u32   = 4;
const PIN_I2C_SCL: u32   = 5;
const PIN_LED_SDB: u32   = 6;
const PIN_ACC_INT: u32   = 10;
const PIN_BTN: u32       = 11;
const PIN_CHG: u32       = 12;
const PIN_PGOOD: u32     = 13;
const PIN_VBAT_EN: u32   = 14;
const PIN_VBAT_ADC: u32  = 26;
const PIN_LIGHT_ADC: u32 = 27;

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
    // Configure digital pads (clear RP2350 ISO bit 8, enable IE bit 6, 4 mA drive, slow slew)
    for &pin in &[
        PIN_LIGHT_PWR, PIN_ACC_SDA, PIN_ACC_SCL, PIN_I2C_SDA, PIN_I2C_SCL,
        PIN_LED_SDB, PIN_ACC_INT, PIN_BTN, PIN_CHG, PIN_PGOOD, PIN_VBAT_EN,
    ] {
        let mut pad = (1 << 6) | (1 << 4); // IE=1, DRIVE=4mA, ISO=0, SLEWFAST=0
        if pin == PIN_BTN || pin == PIN_CHG || pin == PIN_PGOOD || pin == PIN_ACC_INT {
            pad |= 1 << 3; // PUE=1 internal pull-up on active-low status/button inputs
        }
        mmio_write(PADS_BANK0_BASE + 0x04 + 4 * pin, pad);
    }
    // Analog ADC inputs GPIO26 (VBAT_SENSE) & GPIO27 (LIGHT): OD=1 (bit 7), IE=0, ISO=0
    for &apin in &[PIN_VBAT_ADC, PIN_LIGHT_ADC] {
        mmio_write(PADS_BANK0_BASE + 0x04 + 4 * apin, 1 << 7);
    }

    // Clear SIO outputs first; drive LIGHT_PWR=0, LED_SDB=0, VBAT_EN=0; open-drain ACC_SDA/SCL out=0, oe=0
    mmio_write(
        SIO_BASE + 0x18 + 0x08, // GPIO_OUT_CLR (0xD000_0020)
        (1 << PIN_LIGHT_PWR) | (1 << PIN_ACC_SDA) | (1 << PIN_ACC_SCL)
            | (1 << PIN_LED_SDB) | (1 << PIN_VBAT_EN),
    );
    mmio_write(
        SIO_BASE + 0x38, // GPIO_OE_SET: push-pull outputs for power gates & LED_SDB
        (1 << PIN_LIGHT_PWR) | (1 << PIN_LED_SDB) | (1 << PIN_VBAT_EN),
    );
    mmio_write(
        SIO_BASE + 0x40, // GPIO_OE_CLR: release open-drain ACC_SDA/ACC_SCL & inputs
        (1 << PIN_ACC_SDA) | (1 << PIN_ACC_SCL) | (1 << PIN_BTN) | (1 << PIN_CHG) | (1 << PIN_PGOOD),
    );

    // IO_BANK0 FUNCSEL = 5 (SIO) for control/sensor pins; FUNCSEL = 6 (PIO0) for GPIO4/5 (1 MHz I2C_SDA/SCL)
    for &pin in &[
        PIN_LIGHT_PWR, PIN_ACC_SDA, PIN_ACC_SCL, PIN_LED_SDB,
        PIN_ACC_INT, PIN_BTN, PIN_CHG, PIN_PGOOD, PIN_VBAT_EN,
    ] {
        mmio_write(IO_BANK0_BASE + 0x04 + 8 * pin, 5);
    }
    mmio_write(IO_BANK0_BASE + 0x04 + 8 * PIN_I2C_SDA, 6); // PIO0
    mmio_write(IO_BANK0_BASE + 0x04 + 8 * PIN_I2C_SCL, 6); // PIO0

    // Enable ADC block
    mmio_write(ADC_BASE + 0x00, 1); // CS.EN = 1
}

// ============================================================================
// Bus 1: 400 kHz Open-Drain SIO I2C Master on GPIO2/GPIO3 (LIS2DW12TR @ 0x19)
// ============================================================================

#[inline(always)]
fn acc_sda_drive_low(low: bool) {
    if low {
        mmio_write(SIO_BASE + 0x38, 1 << PIN_ACC_SDA); // OE_SET -> drives 0
    } else {
        mmio_write(SIO_BASE + 0x40, 1 << PIN_ACC_SDA); // OE_CLR -> 4.7k pull-up to 3.3V
    }
}

#[inline(always)]
fn acc_scl_drive_low(low: bool) {
    if low {
        mmio_write(SIO_BASE + 0x38, 1 << PIN_ACC_SCL);
    } else {
        mmio_write(SIO_BASE + 0x40, 1 << PIN_ACC_SCL);
    }
}

#[inline(always)]
fn acc_sda_read() -> bool {
    ((mmio_read(SIO_BASE + 0x04) >> PIN_ACC_SDA) & 1) != 0
}

#[inline(always)]
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}

// ============================================================================
// Bus 0: 1.04 MHz Fm+ PIO0 SM0 + DMA Channel 0 Open-Drain I2C Engine (GPIO4/5)
// ============================================================================
//
// PIO0 SM0 runs a 2-instruction open-drain phase engine:
//   0: OUT PINDIRS, 2 [1]   (0x6182: 2 PIO cycles; bit0=SDA_oe, bit1=SCL_oe; pad_out fixed at 0!)
//   1: IN  PINS,    2 [1]   (0x4102: 2 PIO cycles; samples live GPIO4/5 into ISR!)
// At CLKDIV = 9.0 (150 MHz / 9 = 16.67 MHz PIO clk), each 2-bit phase takes 4 PIO cycles = 36 CPU
// cycles (240 ns), so 4 phases = 1 full I2C bit = 960 ns = 1.0417 MHz I2C Fast-mode Plus!

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    fast_sinf(x + 1.570_796_4)
}

/// Read 8x-oversampled RP2350 ADC channel (0 = GPIO26 VBAT_SENSE, 1 = GPIO27 LIGHT).
/// Oversampling 8x averages out the 148 mV / 2 ns VREG_LX buck spikes found in Phase P2!
fn read_adc_oversampled_8x(ch: u32) -> u16 {
    unsafe {
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    init_peripherals_and_pins();
    init_pio0_i2c_master();

    // Gate ON VBAT_EN (GPIO14), LIGHT_PWR (GPIO1), and AW20198 hardware enable LED_SDB (GPIO6)!
    mmio_write(
        SIO_BASE + 0x18, // GPIO_OUT_SET
        (1 << PIN_VBAT_EN) | (1 << PIN_LIGHT_PWR) | (1 << PIN_LED_SDB),
    );
    delay_us(1200); // t_init after SDB rises (AW20198 datasheet >= 1 ms)

    // 5. Bring up LIS2DW12TR accelerometer on GPIO2/3 (0x19)
    unsafe { write_volatile(&mut (*mbox()).boot_stage, 3) };
    let mut who = [0u8; 1];
    let _ = lis2dw12_read_regs(0x0F, &mut who);
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    let mut frame_idx: u32 = 0;

    loop {
        // Sample GPIO status inputs (BTN active-low on GPIO11, CHG GPIO12, PGOOD GPIO13)
        let gpio_in = mmio_read(SIO_BASE + 0x04);
        let btn_pressed = ((gpio_in >> PIN_BTN) & 1) == 0;
        let chg_active = ((gpio_in >> PIN_CHG) & 1) == 0;
        let pgood_active = ((gpio_in >> PIN_PGOOD) & 1) == 0;
        if btn_pressed && !prev_btn_pressed {
            mode = (mode + 1) & 3;
        }
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
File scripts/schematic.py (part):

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    else:
        s.wire(j1.pin("B7"), u7.pin("1"))
        s.wire(j1.pin("A6"), u7.pin("3"))
    s.label("USB_DM_C", (74.93, u7.pin("1")[1]))
    s.label("USB_DP_C", (74.93, u7.pin("3")[1]))
    s.wire(u7.pin("5"), (86.36, vbus_y))
    s.power("power:GND", u7.pin("2"))
    for pin, net in (("6", "USB_DM"), ("4", "USB_DP")):
        p = u7.pin(pin)
        s.wire(p, (p[0] + 5.08, p[1]))
        s.label(net, (p[0] + 5.08, p[1]), **GL)
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    s.text("USB500: 450-500 mA in. 297 mA charge, ILIM must not float.\nTMR open: default 5 h. TS fixed: no NTC.", (116.84, 124.46))
    s.power("power:GND", u5.pin("VSS"))
    # Status, pulled to 3V3 at the charger. CHG's wire crosses PGOOD's.
    pg, ch = u5.pin("~{PGOOD}"), u5.pin("~{CHG}")
    for p, net in ((pg, "PGOOD"), (ch, "CHG")):
        s.wire(p, (205.74, p[1]))
        s.label(net, (205.74, p[1]), **GL)
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    s.wire(ng, (ng[0], bat_n_y))
    s.wire(n, (n[0] + 2.54, n[1]), (n[0] + 2.54, bat_n_y), (ng[0], bat_n_y))
    s.wire(c6.pin("2"), (c6.pin("2")[0], bat_n_y))
    s.label("BAT_N", (58.42, bat_n_y))
    vm = u8.pin("VM")
    s.wire(vm, (vm[0] + 7.62, vm[1]))
    s.power("power:GND", (vm[0] + 7.62, vm[1]))
    s.text("BAT_N: cell minus. Pins 4, 5 and the pad. Never pour GND here,\nor protection is bypassed (protection.md).", (58.42, bat_n_y + 5.08))
    s.box((15.24, by - 12.7), (129.54, bat_n_y + 15.24), "CELL AND PROTECTION")

    # Switched VBAT sense: N pulls the P gate down; P feeds the divider.
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    # N gate: VBAT_EN, held low by R9 when the MCU is off.
    g1 = qn.pin("G")
    s.wire(g1, (139.7, g1[1]))
    s.label("VBAT_EN", (139.7, g1[1]), rot=180, **GL)
    s.res_v("R9", "100k", (146.05, g1[1]), text_left=True, to_gnd=True)
    s.power("power:GND", qn.pin("S"))
    # Divider off the P drain.
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    s.res_v("R12", "100k", (dx, mid), to_gnd=True)
    s.wire((dx, mid), (dx + 15.24, mid))
    s.cap("C7", "100n", (dx + 10.16, mid))
    s.label("VBAT_SENSE", (dx + 15.24, mid), **GL)
    s.text("Zero draw off. ADC reads true only while 3V3 regulates,\nVBAT >= 3.5 V (intent R22). Wait >= 5 ms after enabling.", (139.7, by + 52.07))
    s.box((130.81, by - 12.7), (241.3, by + 58.42), "VBAT SENSE")
    return s
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    s.power("power:+3V3", (83.82, rail))
    s.wire((vin[0], 86.36), (vin[0] - 6.35, 86.36))
    s.cap("C16", "4.7u", (vin[0] - 6.35, 86.36), fp=C0402S, decouples="U3.49")
    av = u.pin("VREG_AVDD")
    s.res_v("R13", "33R", (av[0], rail))
    s.wire((av[0], rail + 7.62), av)
    s.wire((av[0], 99.06), (av[0] - 7.62, 99.06))
    s.cap("C17", "4.7u", (av[0] - 7.62, 99.06), text_left=True, decouples="U3.46")
    s.label("VREG_AVDD", (av[0], 97.79), rot=90)
    s.power("power:PWR_FLAG", (av[0] - 7.62, 99.06), value="PWR_FLAG")
    serves = [("C8", "1"), ("C9", "11"), ("C10", "20"), ("C11", "30"), ("C12", "38"), ("C13", "53"), ("C14", "44")]
    for i, (ref, pin) in enumerate(serves):
        s.cap(ref, "100n", (88.9 + 8.89 * i, rail), decouples=f"U3.{pin}")
    s.text("100 nF at IOVDD pins 1, 11, 20, 30, 38 (C8-C12), USB_OTP_VDD 53\nand QSPI_IOVDD 54 (C13), ADC_AVDD 44 and IOVDD 45 (C14).", (83.82, 66.04))
    lx, fb, dv = u.pin("VREG_LX"), u.pin("VREG_FB"), u.pin("DVDD")
    y_lx, y_fb, x1 = 71.12, 88.9, dv[0] + 5.08
    s.wire(lx, (lx[0], y_lx))
    l1 = s.symbol("Device:L", "L1", "3.3u", ((lx[0] + x1) / 2, y_lx), rot=270, footprint="round_pendant:L_pol_2016",
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                  ref_at=((lx[0] + x1) / 2, y_lx - 5.08), value_at=((lx[0] + x1) / 2, y_lx - 2.54), justify="")
    s.wire((lx[0], y_lx), l1.pin("2"))
    s.wire(l1.pin("1"), (x1, y_lx))
    s.label("VREG_LX", (lx[0], 96.52), rot=90)
    s.wire(fb, (fb[0], y_fb), (x1, y_fb), (x1, y_lx))
    s.wire(dv, (dv[0], y_fb))
    s.wire((x1, y_lx), (x1 + 50.8, y_lx))
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                s.label(used[i], (p[0] + 22.86, p[1]))
        elif i == 26:
            s.wire(p, (p[0] + 7.62, p[1]))
            s.label("VBAT_SENSE", (p[0] + 7.62, p[1]), **GL)
        else:
            s.no_connect(p)
    # I2C0 pull-ups live here, at the master.
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        s.wire(p, (p[0] - 7.62, p[1]))
        s.label(nm, (p[0] - 7.62, p[1]), rot=180)
    # USB.
    dm, dp = u.pin("USB_DM"), u.pin("USB_DP")
    r4 = s.res_h("R14", "27R", (dm[0] - 26.67, dm[1]))
    s.wire(dm, r4.pin("2"))
    s.wire(r4.pin("1"), (r4.pin("1")[0] - 5.08, dm[1]))
    s.label("USB_DM", (r4.pin("1")[0] - 5.08, dm[1]), rot=180, **GL)
    r5 = s.res_h("R15", "27R", (dp[0] - 26.67, dp[1]), text_below=True)
    s.wire(dp, r5.pin("2"))
    s.wire(r5.pin("1"), (r5.pin("1")[0] - 5.08, dp[1]))
    s.label("USB_DP", (r5.pin("1")[0] - 5.08, dp[1]), rot=180, **GL)
    s.label("USB_DM_MCU", (dm[0] - 5.08, dm[1]), rot=180)
    s.label("USB_DP_MCU", (dp[0] - 5.08, dp[1]), rot=180)

    # Flash.
    ss = u.pin("~{QSPI_SS}")
    fx, fy = 93.98, ss[1] + 7.62
    u4 = s.symbol("Memory_Flash:W25Q128JVS", "U4", "W25Q128JVPIQ", (fx, fy), mirror="y",
                  footprint="round_pendant:WSON-8_6x5mm_P1.27mm_NoEPCopper",
                  fields={"LCSC": "C190862", "MPN": "W25Q128JVPIQ", "Manufacturer": "Winbond"},
                  ref_at=(fx - 8.89, fy + 13.97), value_at=(fx - 8.89, fy + 16.51), justify="right")
    for fpin, upin, lab in (("1", "~{QSPI_SS}", "QSPI_SS"), ("6", "QSPI_SCLK", "QSPI_SCLK"), ("5", "QSPI_SD0", "QSPI_SD0"),
                            ("2", "QSPI_SD1", "QSPI_SD1"), ("3", "QSPI_SD2", "QSPI_SD2"), ("7", "QSPI_SD3", "QSPI_SD3")):
        a, b = u4.pin(fpin), u.pin(upin)
        assert abs(a[1] - b[1]) < 1e-6, (fpin, a, b)
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    # SCL and SDA leave to the left under the pull-ups, which sit at the sensor.
    bx0 = hx - 22.86
    # hx carries 3V3 down the left side of the chip, so the bus pins jog under it on a
    # pair of labels: SCL and SDA run to their pull-ups without crossing it twice.
    for pin, net, x, ref in ((scl, "ACC_SCL", hx - 5.08, "R19"), (sda, "ACC_SDA", hx - 15.24, "R20")):
        s.wire(pin, (bx0, pin[1]))
        s.label(net, (bx0, pin[1]), rot=180)
        s.res_v(ref, "4.7k", (x, top), text_left=(net == "ACC_SDA"))
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        s.wire((x, top + 7.62), (x, pin[1]))
    i1 = u9.pin("INT1")
    s.wire(i1, (i1[0] + 7.62, i1[1]))
    s.label("ACC_INT", (i1[0] + 7.62, i1[1]))
    s.no_connect(u9.pin("INT2"))
    g = u9.pin("GND")
    s.power("power:GND", g)
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
    # Buttons.
    y = 147.32
    s.label("BTN", (284.48, y), rot=180)
    r = s.res_h("R18", "1k", (284.48, y))
    sw1 = s.symbol("Switch:SW_Push", "SW1", "USER / WAKE", (306.07, y), footprint=BTN_FP,
                   fields=BTN_FIELDS,
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    s.wire(q, (q[0] + 2.54, q[1]))
    s.power("power:GND", (q[0] + 2.54, q[1]))
    y = 160.02
    s.label("QSPI_SS", (284.48, y), rot=180)
    r = s.res_h("R16", "1k", (284.48, y), text_below=True)
    sw2 = s.symbol("Switch:SW_Push", "SW2", "BOOTSEL", (306.07, y), footprint=BTN_FP,
                   fields=BTN_FIELDS,
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
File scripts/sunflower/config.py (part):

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    centre_led: bool = False
    usb_c: bool = False
    als_pos: Tuple[float, float, float] | None = None
    vbat_en_gpio: int = 14  # RP2350 GPIO switching the VBAT divider (s2-110-usbc: GPIO28, pin 42, routes beside VBAT_SENSE)
    # Bring-up pads (2026-11-07, s2-110-usbc): test points for UART1, I2C0, VBUS and a spare ADC GPIO (TP_GPIOS),
    # and board ID straps. ID_GPIOS are read with internal pull-ups; the ones in id_tied are tied to GND (bit = 0),
    # the rest left open (bit = 1). Boards without straps read all ones.
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# USB-C study: s2-110 with a USB-C receptacle at the south rim, an LED at the centre and the light sensor at the top rim.
VARIANTS["s2-110-usbc"] = _v("s2-110-usbc", "S3C", 110, (5, 5),
                             "110 XL-1615RGBC-RF LEDs in a 38 mm sunflower with a centre LED, USB-C on the back, light sensor at the rim, 2x AW20198QNR, 4-layer JLCPCB",
                             centre_led=True, usb_c=True, als_pos=(0.0, -18.20, 0.0), vbat_en_gpio=28,
                             test_pads=True, id_tied=(19,))

# Board ID straps: GPIO19..21 (RP2350A pins 31-33, east side, next to the exposed GND pad). Read with pull-ups,
# ID = GPIO19 | GPIO20 << 1 | GPIO21 << 2; a tied pin reads 0. 0b111 = no straps (every board before s2-110-usbc).
ID_GPIOS = (19, 20, 21)
# Test-pad GPIOs on boards with test_pads: UART1 on GPIO24 (TX) and GPIO25 (RX), and GPIO29, the only free ADC input.
TP_GPIOS = {24: "UART_TX", 25: "UART_RX", 29: "GPIO29_TP"}
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# 2x AW20198) with the LED field taken from the pattern explorer's dense Penrose P3 vertices. ID strap GPIO20 (ID = 5).
VARIANTS["pn-dense"] = _v("pn-dense", "PN", 0, (4, 4),
                          "Dense Penrose P3 tiling of XL-1615RGBC-RF LEDs (rhomb vertices, 2.547 mm closest pair) in a 38 mm disc, USB-C on the back, light sensor at the rim, 2x AW20198QNR, 4-layer JLCPCB",
                          centre_led=True, usb_c=True, als_pos=(0.0, -18.20, 0.0), vbat_en_gpio=28,
                          test_pads=True, id_tied=(20,), layout="penrose")
VARIANTS["pn-dense"] = dataclasses.replace(
    VARIANTS["pn-dense"], n=len(penrose_points(front_keepouts(VARIANTS["pn-dense"]))))
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    VARIANTS["pn-dense"], summary=VARIANTS["pn-dense"].summary.replace("Dense", f"{VARIANTS['pn-dense'].n}-LED dense", 1))


# One driver: pn-dense with U2 removed and the centre LED driven directly by GPIO7/8/9 (R, G, B), so the matrix is 66 LEDs
# in 6 wedges of 11 on U1. Board ID strap GPIO21 (ID = 3).
VARIANTS["pn-dense-1d"] = _v("pn-dense-1d", "PN1", 66, (6,),
                             "67-LED dense Penrose P3 tiling of XL-1615RGBC-RF LEDs (rhomb vertices, 2.547 mm closest pair) in a 38 mm disc: 66 on 1x AW20198QNR, the centre LED on RP2350 GPIO7/8/9; USB-C on the back, light sensor at the rim, 4-layer JLCPCB",
                             centre_led=True, usb_c=True, als_pos=(0.0, -18.20, 0.0), vbat_en_gpio=28,
                             test_pads=True, id_tied=(21,), layout="penrose", direct_led=(7, 8, 9))
assert len(spec_points(VARIANTS["pn-dense-1d"])) == 66
# Direct LED parts: the LED takes the next D number after the matrix; R/G/B series resistors (direct-led.md).
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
